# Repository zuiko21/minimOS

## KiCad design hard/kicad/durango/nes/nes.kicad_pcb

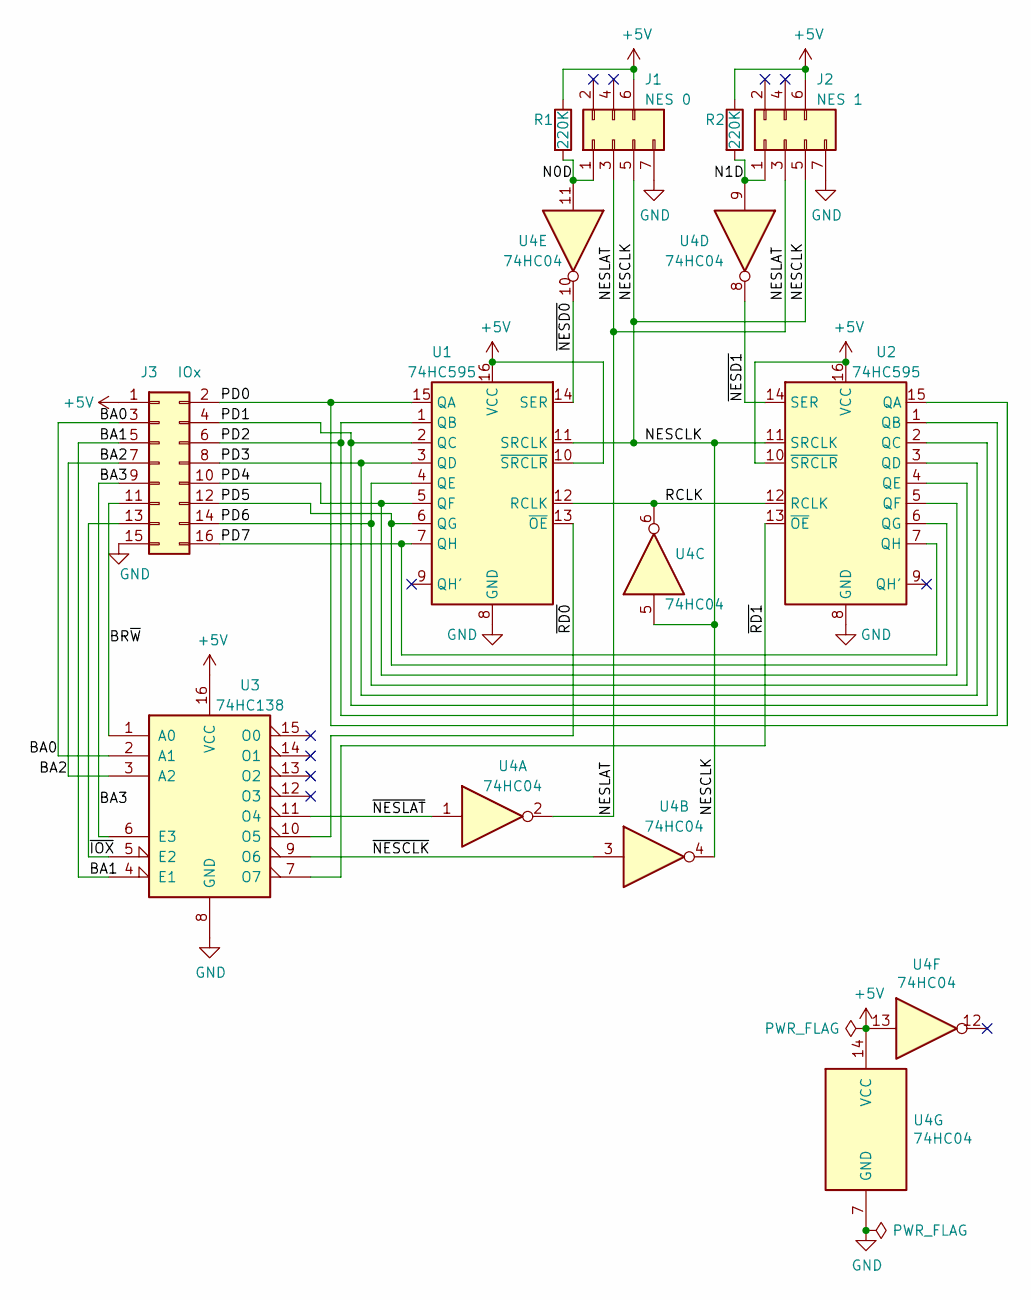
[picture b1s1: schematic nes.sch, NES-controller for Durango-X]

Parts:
J1: NES 0; PinSocket_2x04_P2.54mm_Vertical
J2: NES 1; PinSocket_2x04_P2.54mm_Vertical
J3: IOx; IDC-Header_2x08_P2.54mm_Vertical
R1, R2: 220K; R_Axial_DIN0204_L3.6mm_D1.6mm_P2.54mm_Vertical
U1, U2: 74HC595; DIP-16_W7.62mm_Socket
U3: 74HC138; DIP-16_W7.62mm_Socket
U4: 74HC04; DIP-14_W7.62mm_Socket

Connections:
+5V: J1.6, J2.6, J3.1, R1.1, R2.1, U1.10 (~SRCLR), U1.16 (VCC), U2.10 (~SRCLR), U2.16 (VCC), U3.16 (VCC), U4.13, U4.14 (VCC)
/BA0: J3.3, U3.2 (A1)
/BA1: J3.5, U3.4 (E1)
/BA2: J3.7, U3.3 (A2)
/BA3: J3.9, U3.6 (E3)
/BR~W: J3.11, U3.1 (A0)
/N0D: J1.1, R1.2, U4.11
/N1D: J2.1, R2.2, U4.9
/NESCLK: J1.5, J2.5, U1.11 (SRCLK), U2.11 (SRCLK), U4.4, U4.5
/NESLAT: J1.3, J2.3, U4.2
/PD0: J3.2, U1.15 (QA), U2.15 (QA)
/PD1: J3.4, U1.2 (QC), U2.2 (QC)
/PD2: J3.6, U1.1 (QB), U2.1 (QB)
/PD3: J3.8, U1.3 (QD), U2.3 (QD)
/PD4: J3.10, U1.5 (QF), U2.5 (QF)
/PD5: J3.12, U1.6 (QG), U2.6 (QG)
/PD6: J3.14, U1.4 (QE), U2.4 (QE)
/PD7: J3.16, U1.7 (QH), U2.7 (QH)
/RCLK: U1.12 (RCLK), U2.12 (RCLK), U4.6
/~IOX: J3.13, U3.5 (E2)
/~NESCLK: U3.9 (O6), U4.3
/~NESD0: U1.14 (SER), U4.10
/~NESD1: U2.14 (SER), U4.8
/~NESLAT: U3.11 (O4), U4.1
/~RD0: U1.13 (~OE), U3.10 (O5)
/~RD1: U2.13 (~OE), U3.7 (O7)
GND: J1.7, J2.7, J3.15, U1.8 (GND), U2.8 (GND), U3.8 (GND), U4.7 (GND)

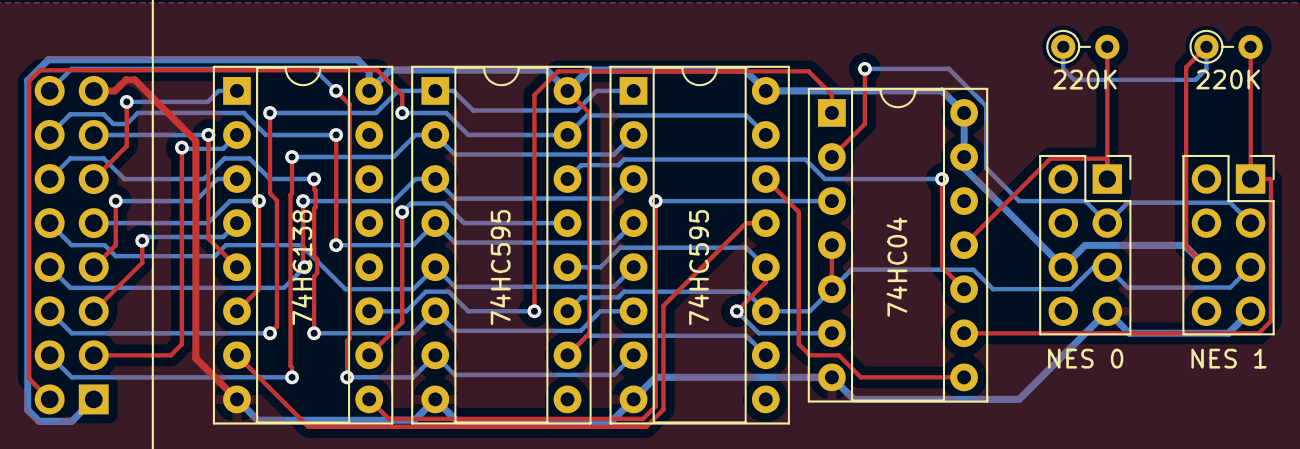
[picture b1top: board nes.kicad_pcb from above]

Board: 2 copper layers, 9 parts (0 on the bottom side), 27 nets.

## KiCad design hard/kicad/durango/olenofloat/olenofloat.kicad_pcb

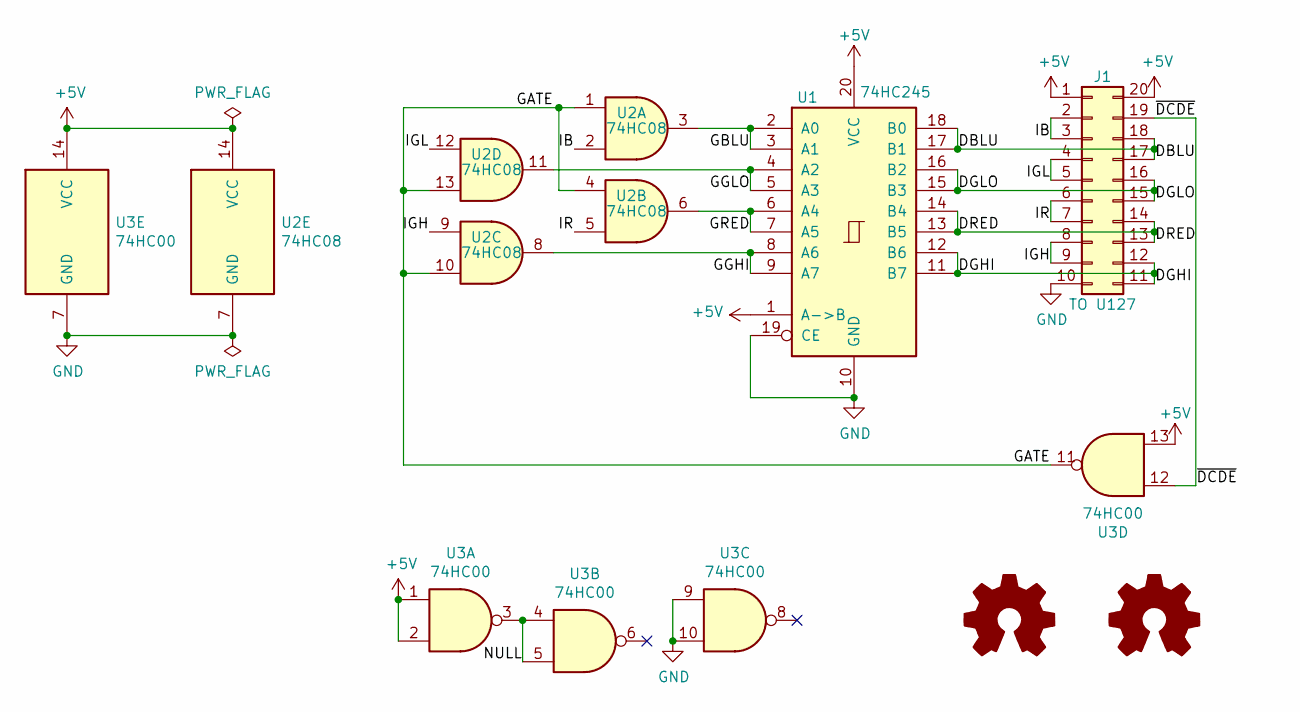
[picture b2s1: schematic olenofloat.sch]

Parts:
J1: TO U127; DIP-20_W7.62mm_Socket_LongPads
LOGO1: Logo_Open_Hardware_Small; j300
LOGO2: Logo_Open_Hardware_Small; OSHW-Symbol_6.7x6mm_SilkScreen
U1: 74HC245; DIP-20_W7.62mm_Socket
U2: 74HC08; DIP-14_W7.62mm_Socket
U3: 74HC00; DIP-14_W7.62mm_Socket

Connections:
+5V: J1.1, J1.20, U1.1 (A->B), U1.20 (VCC), U2.14 (VCC), U3.1, U3.2, U3.13, U3.14 (VCC)
/DBLU: J1.17, J1.18, U1.17 (B1), U1.18 (B0)
/DGHI: J1.11, J1.12, U1.11 (B7), U1.12 (B6)
/DGLO: J1.15, J1.16, U1.15 (B3), U1.16 (B2)
/DRED: J1.13, J1.14, U1.13 (B5), U1.14 (B4)
/GATE: U2.1, U2.4, U2.10, U2.13, U3.11
/GBLU: U1.2 (A0), U1.3 (A1), U2.3
/GGHI: U1.8 (A6), U1.9 (A7), U2.8
/GGLO: U1.4 (A2), U1.5 (A3), U2.11
/GRED: U1.6 (A4), U1.7 (A5), U2.6
/IB: J1.2, J1.3, U2.2
/IGH: J1.8, J1.9, U2.9
/IGL: J1.4, J1.5, U2.12
/IR: J1.6, J1.7, U2.5
/NULL: U3.3, U3.4, U3.5
/~DCDE: J1.19, U3.12
GND: J1.10, U1.10 (GND), U1.19 (CE), U2.7 (GND), U3.7 (GND), U3.9, U3.10

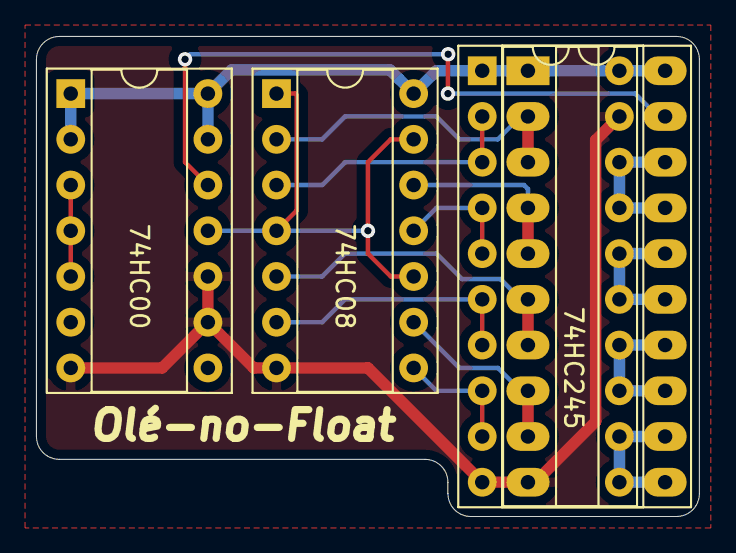
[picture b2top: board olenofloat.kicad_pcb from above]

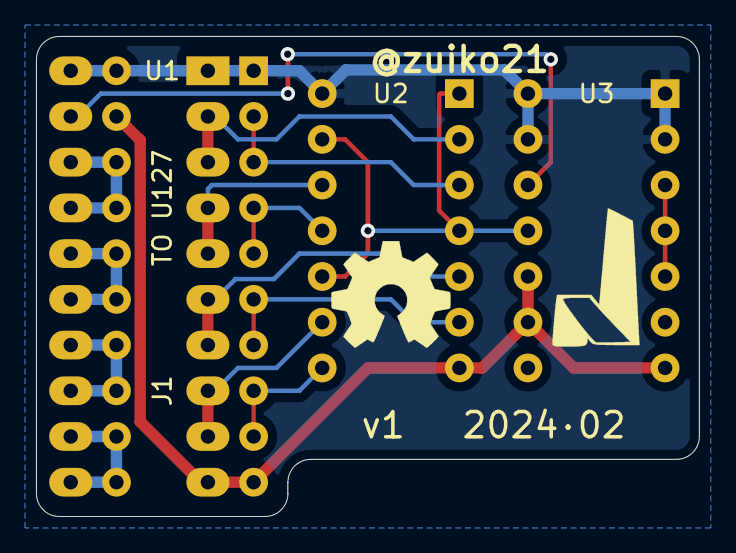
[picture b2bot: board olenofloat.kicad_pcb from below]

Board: 2 copper layers, 36.8 x 26.7 mm, 6 parts (2 on the bottom side), 17 nets.

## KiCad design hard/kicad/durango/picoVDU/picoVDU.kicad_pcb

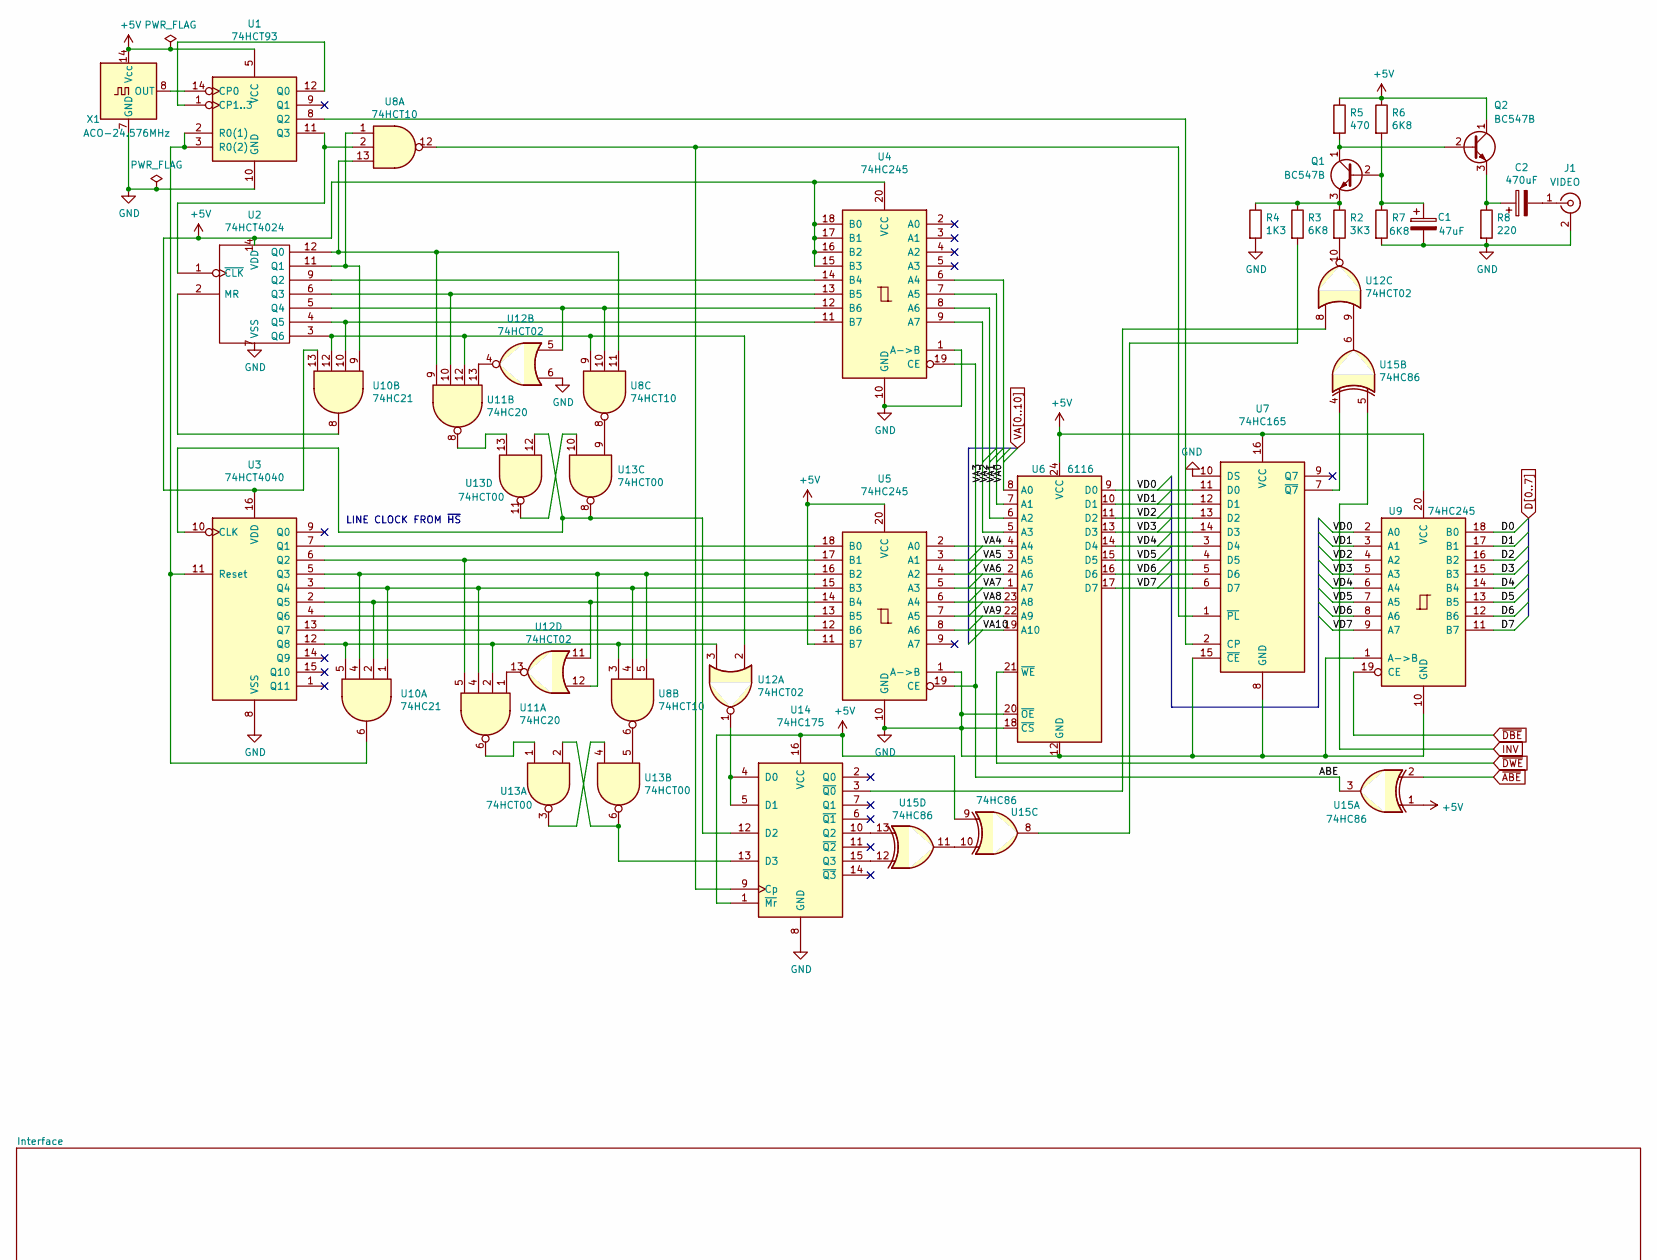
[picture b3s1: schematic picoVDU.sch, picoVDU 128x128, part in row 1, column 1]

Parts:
C1: 47uF; CP_Radial_D8.0mm_P5.00mm
C2: 470uF; CP_Radial_D12.5mm_P5.00mm
J1: VIDEO; SMA_Amphenol_132289_EdgeMount
Q1, Q2: BC547B; TO-92_Inline
R2: 3K3; R_Axial_DIN0309_L9.0mm_D3.2mm_P2.54mm_Vertical
R3, R6, R7: 6K8; R_Axial_DIN0309_L9.0mm_D3.2mm_P2.54mm_Vertical
R4: 1K3; R_Axial_DIN0309_L9.0mm_D3.2mm_P2.54mm_Vertical
R5: 470; R_Axial_DIN0309_L9.0mm_D3.2mm_P2.54mm_Vertical
R8: 220; R_Axial_DIN0309_L9.0mm_D3.2mm_P2.54mm_Vertical
U1: 74HCT93; DIP-14_W7.62mm_Socket
U2: 74HCT4024; DIP-14_W7.62mm_Socket
U3: 74HCT4040; DIP-16_W7.62mm_Socket
U4, U5, U9: 74HC245; DIP-20_W7.62mm_Socket
U6: 6116; DIP-24_W15.24mm_Socket
U7: 74HC165; DIP-16_W7.62mm_Socket
U8: 74HCT10; DIP-14_W7.62mm_Socket
U10: 74HC21; DIP-14_W7.62mm_Socket
U11: 74HC20; DIP-14_W7.62mm_Socket
U12: 74HCT02; DIP-14_W7.62mm_Socket
U13: 74HCT00; DIP-14_W7.62mm_Socket
U14: 74HC175; DIP-16_W7.62mm_Socket
U15: 74HC86; DIP-14_W7.62mm_Socket
X1: ACO-24.576MHz; Oscillator_DIP-14

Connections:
+5V: Q2.1 (C), R5.1, R6.1, U1.5 (VCC), U2.14 (VDD), U3.16 (VDD), U4.15 (B3), U4.16 (B2), U4.17 (B1), U4.18 (B0), U4.20 (VCC), U5.11 (B7), U5.20 (VCC), U6.24 (VCC), U7.16 (VCC), U9.20 (VCC), U10.13, U14.1 (~Mr), U14.16 (VCC), U15.1, U15.9, X1.14 (Vcc); also elsewhere on the board
/ABE: U4.19 (CE), U5.19 (CE), U15.3
/VD0: U6.9 (D0), U7.11 (D0), U9.2 (A0)
/VD1: U6.10 (D1), U7.12 (D1), U9.3 (A1)
/VD2: U6.11 (D2), U7.13 (D2), U9.4 (A2)
/VD3: U6.13 (D3), U7.14 (D3), U9.5 (A3)
/VD4: U6.14 (D4), U7.3 (D4), U9.6 (A4)
/VD5: U6.15 (D5), U7.4 (D5), U9.7 (A5)
/VD6: U6.16 (D6), U7.5 (D6), U9.8 (A6)
/VD7: U6.17 (D7), U7.6 (D7), U9.9 (A7)
D0: U9.18 (B0); also elsewhere on the board
D1: U9.17 (B1); also elsewhere on the board
D2: U9.16 (B2); also elsewhere on the board
D3: U9.15 (B3); also elsewhere on the board
D4: U9.14 (B4); also elsewhere on the board
D5: U9.13 (B5); also elsewhere on the board
D6: U9.12 (B6); also elsewhere on the board
D7: U9.11 (B7); also elsewhere on the board
GND: C1.2, J1.2 (Ext), R4.2, R7.2, R8.2, U1.10 (GND), U2.7 (VSS), U3.8 (VSS), U4.1 (A->B), U4.10 (GND), U5.1 (A->B), U5.10 (GND), U6.12 (GND), U6.18 (~CS), U6.20 (~OE), U7.8 (GND), U7.10 (DS), U7.15 (~CE), U9.1 (A->B), U9.10 (GND), U12.6, U14.8 (GND), X1.7 (GND); also elsewhere on the board
INV: U15.5; also elsewhere on the board
unnamed: C1.1, Q1.2 (B), R6.2, R7.1
unnamed: C2.1, Q2.3 (E), R8.1
unnamed: C2.2, J1.1 (In)
unnamed: Q1.1 (C), Q2.2 (B), R5.2
unnamed: Q1.3 (E), R2.1, R3.1, R4.1
unnamed: R2.2, U12.10
unnamed: R3.2, U15.8
unnamed: U1.1 (CP1..3), U1.12 (Q0)
unnamed: U1.2 (R0(1)), U1.3 (R0(2)), U3.11 (Reset), U10.6
unnamed: U1.8 (Q2), U7.2 (CP)
unnamed: U1.11 (Q3), U2.1 (~CLK), U8.2
unnamed: U1.14 (CP0), X1.8 (OUT)
unnamed: U2.9 (Q2), U4.14 (B4)
unnamed: U3.4 (Q6), U5.13 (B5)
unnamed: U3.7 (Q1), U5.18 (B0)
unnamed: U3.13 (Q7), U5.12 (B6)
unnamed: U3.3 (Q4), U5.15 (B3), U8.4, U10.1, U11.4
unnamed: U3.2 (Q5), U5.14 (B4), U10.2, U12.11
unnamed: U3.5 (Q3), U5.16 (B2), U8.5, U10.4, U12.12
unnamed: U3.12 (Q8), U8.3, U10.5, U11.2, U12.3
unnamed: U2.2 (MR), U10.8
unnamed: U2.11 (Q1), U8.1, U10.9
unnamed: U2.4 (Q5), U4.11 (B7), U10.10
unnamed: U2.3 (Q6), U8.9, U10.12, U11.12, U12.2
unnamed: U11.1, U12.13
unnamed: U3.6 (Q2), U5.17 (B1), U11.5
unnamed: U11.6, U13.1
unnamed: U11.8, U13.13
unnamed: U2.12 (Q0), U8.11, U8.13, U11.9
unnamed: U2.6 (Q3), U4.13 (B5), U11.10
unnamed: U11.13, U12.4
unnamed: U12.1, U14.4 (D0), U14.5 (D1)
unnamed: U2.5 (Q4), U4.12 (B6), U8.10, U12.5
unnamed: U12.8, U14.3 (~Q0)
unnamed: U12.9, U15.6
unnamed: U13.2, U13.6, U14.13 (D3)
unnamed: U13.3, U13.4
unnamed: U8.6, U13.5
unnamed: U8.8, U13.9
unnamed: U13.10, U13.11
unnamed: U3.10 (CLK), U13.8, U13.12, U14.12 (D2)
unnamed: U7.1 (~PL), U8.12, U14.9 (Cp)
unnamed: U14.10 (Q2), U15.13
unnamed: U14.15 (Q3), U15.12
unnamed: U7.7 (~Q7), U15.4
unnamed: U15.10, U15.11
VA0: U4.6 (A4), U6.8 (A0); also elsewhere on the board
VA1: U4.7 (A5), U6.7 (A1); also elsewhere on the board
VA2: U4.8 (A6), U6.6 (A2); also elsewhere on the board
VA3: U4.9 (A7), U6.5 (A3); also elsewhere on the board
VA4: U5.2 (A0), U6.4 (A4); also elsewhere on the board
VA5: U5.3 (A1), U6.3 (A5); also elsewhere on the board
VA6: U5.4 (A2), U6.2 (A6); also elsewhere on the board
VA7: U5.5 (A3), U6.1 (A7); also elsewhere on the board
VA8: U5.6 (A4), U6.23 (A8); also elsewhere on the board
VA9: U5.7 (A5), U6.22 (A9); also elsewhere on the board
VA10: U5.8 (A6), U6.19 (A10); also elsewhere on the board
~ABE: U15.2; also elsewhere on the board
~DBE: U6.21 (~WE), U9.19 (CE); also elsewhere on the board

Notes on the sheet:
LINE CLOCK FROM ~HS

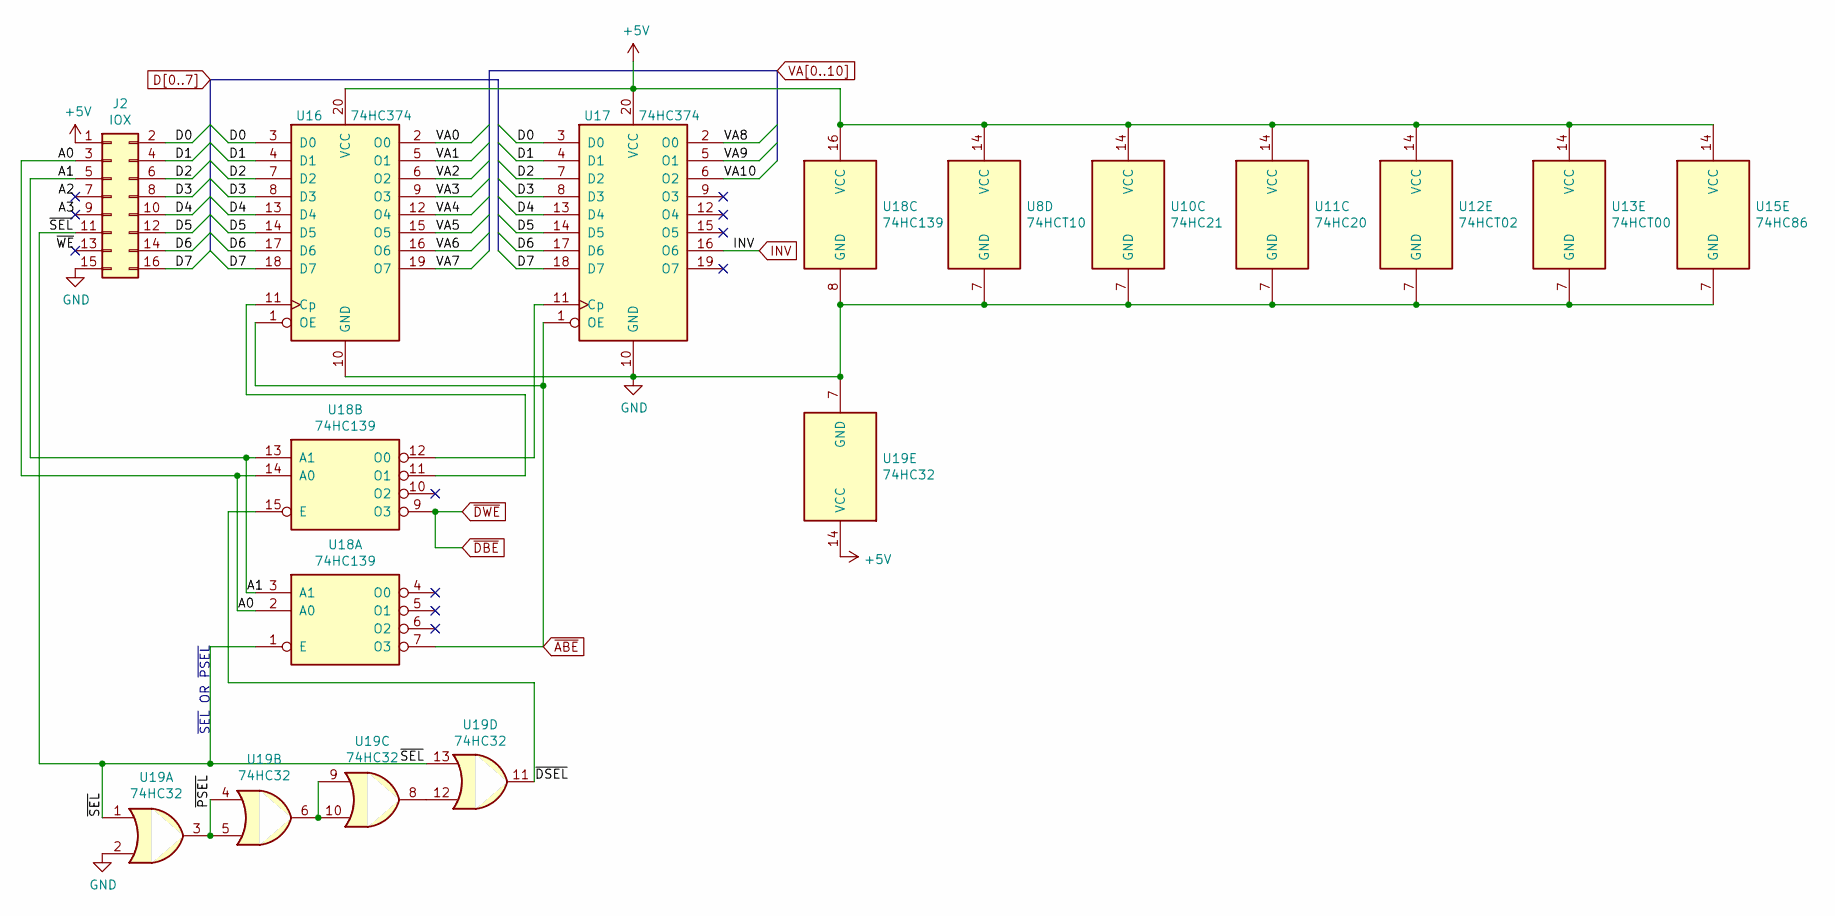
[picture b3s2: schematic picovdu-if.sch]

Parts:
J2: IOX; PinHeader_2x08_P2.54mm_Vertical
U8: 74HCT10; DIP-14_W7.62mm_Socket
U10: 74HC21; DIP-14_W7.62mm_Socket
U11: 74HC20; DIP-14_W7.62mm_Socket
U12: 74HCT02; DIP-14_W7.62mm_Socket
U13: 74HCT00; DIP-14_W7.62mm_Socket
U15: 74HC86; DIP-14_W7.62mm_Socket
U16, U17: 74HC374; DIP-20_W7.62mm_Socket
U18: 74HC139; DIP-16_W7.62mm_Socket
U19: 74HC32; DIP-14_W7.62mm_Socket

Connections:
+5V: J2.1, U8.14 (VCC), U10.14 (VCC), U11.14 (VCC), U12.14 (VCC), U13.14 (VCC), U15.14 (VCC), U16.20 (VCC), U17.20 (VCC), U18.16 (VCC), U19.14 (VCC); also elsewhere on the board
/Interface/A0: J2.3, U18.2 (A0), U18.14 (A0)
/Interface/A1: J2.5, U18.3 (A1), U18.13 (A1)
/Interface/A2: J2.7
/Interface/A3: J2.9
/Interface/~DSEL: U18.15 (E), U19.11
/Interface/~PSEL: U19.3, U19.4, U19.5
/Interface/~SEL: J2.11, U18.1 (E), U19.1, U19.13
/Interface/~WE: J2.13
D0: J2.2, U16.3 (D0), U17.3 (D0); also elsewhere on the board
D1: J2.4, U16.4 (D1), U17.4 (D1); also elsewhere on the board
D2: J2.6, U16.7 (D2), U17.7 (D2); also elsewhere on the board
D3: J2.8, U16.8 (D3), U17.8 (D3); also elsewhere on the board
D4: J2.10, U16.13 (D4), U17.13 (D4); also elsewhere on the board
D5: J2.12, U16.14 (D5), U17.14 (D5); also elsewhere on the board
D6: J2.14, U16.17 (D6), U17.17 (D6); also elsewhere on the board
D7: J2.16, U16.18 (D7), U17.18 (D7); also elsewhere on the board
GND: J2.15, U8.7 (GND), U10.7 (GND), U11.7 (GND), U12.7 (GND), U13.7 (GND), U15.7 (GND), U16.10 (GND), U17.10 (GND), U18.8 (GND), U19.2, U19.7 (GND); also elsewhere on the board
INV: U17.16 (O6); also elsewhere on the board
unnamed: U16.11 (Cp), U18.11 (O1)
unnamed: U17.11 (Cp), U18.12 (O0)
unnamed: U19.6, U19.9, U19.10
unnamed: U19.8, U19.12
VA0: U16.2 (O0); also elsewhere on the board
VA1: U16.5 (O1); also elsewhere on the board
VA2: U16.6 (O2); also elsewhere on the board
VA3: U16.9 (O3); also elsewhere on the board
VA4: U16.12 (O4); also elsewhere on the board
VA5: U16.15 (O5); also elsewhere on the board
VA6: U16.16 (O6); also elsewhere on the board
VA7: U16.19 (O7); also elsewhere on the board
VA8: U17.2 (O0); also elsewhere on the board
VA9: U17.5 (O1); also elsewhere on the board
VA10: U17.6 (O2); also elsewhere on the board
~ABE: U16.1 (OE), U17.1 (OE), U18.7 (O3); also elsewhere on the board
~DBE: U18.9 (O3); also elsewhere on the board

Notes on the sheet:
~SEL~ OR ~PSEL

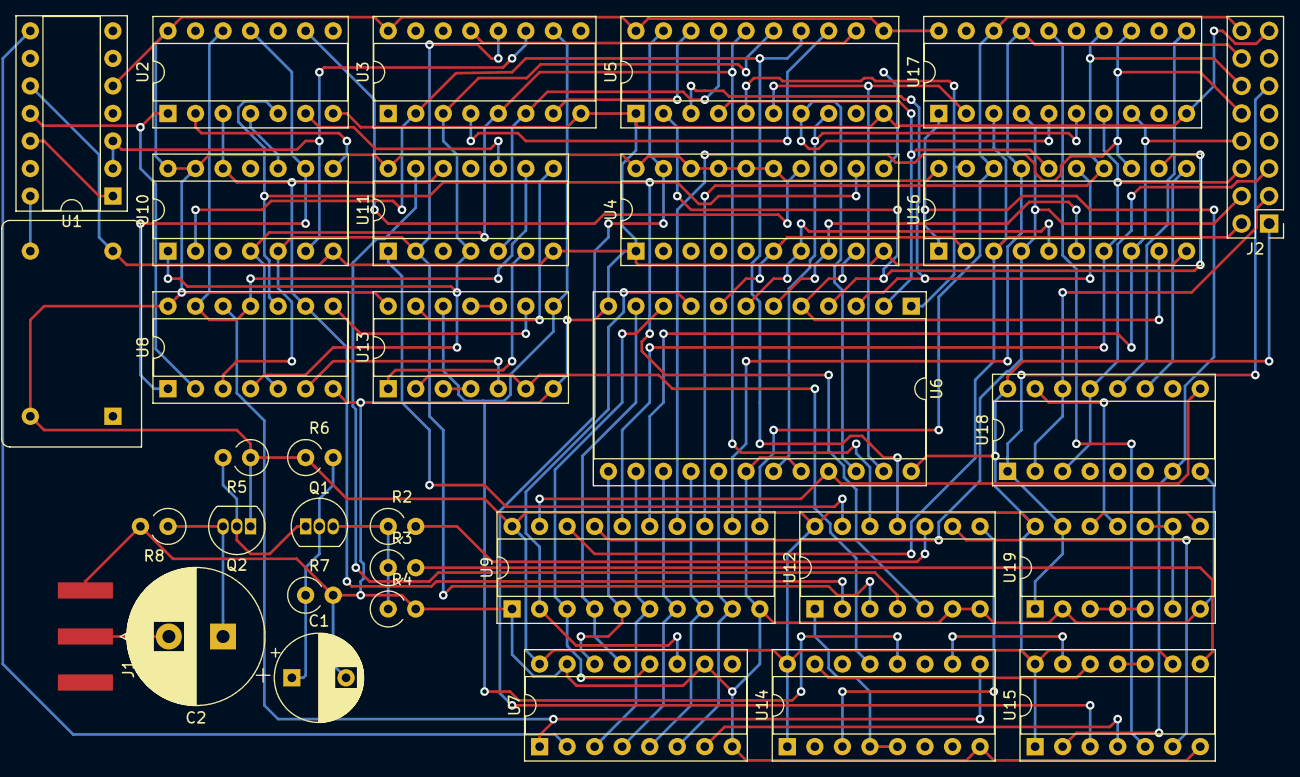
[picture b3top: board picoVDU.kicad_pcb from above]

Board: 2 copper layers, 33 parts (0 on the bottom side), 88 nets.

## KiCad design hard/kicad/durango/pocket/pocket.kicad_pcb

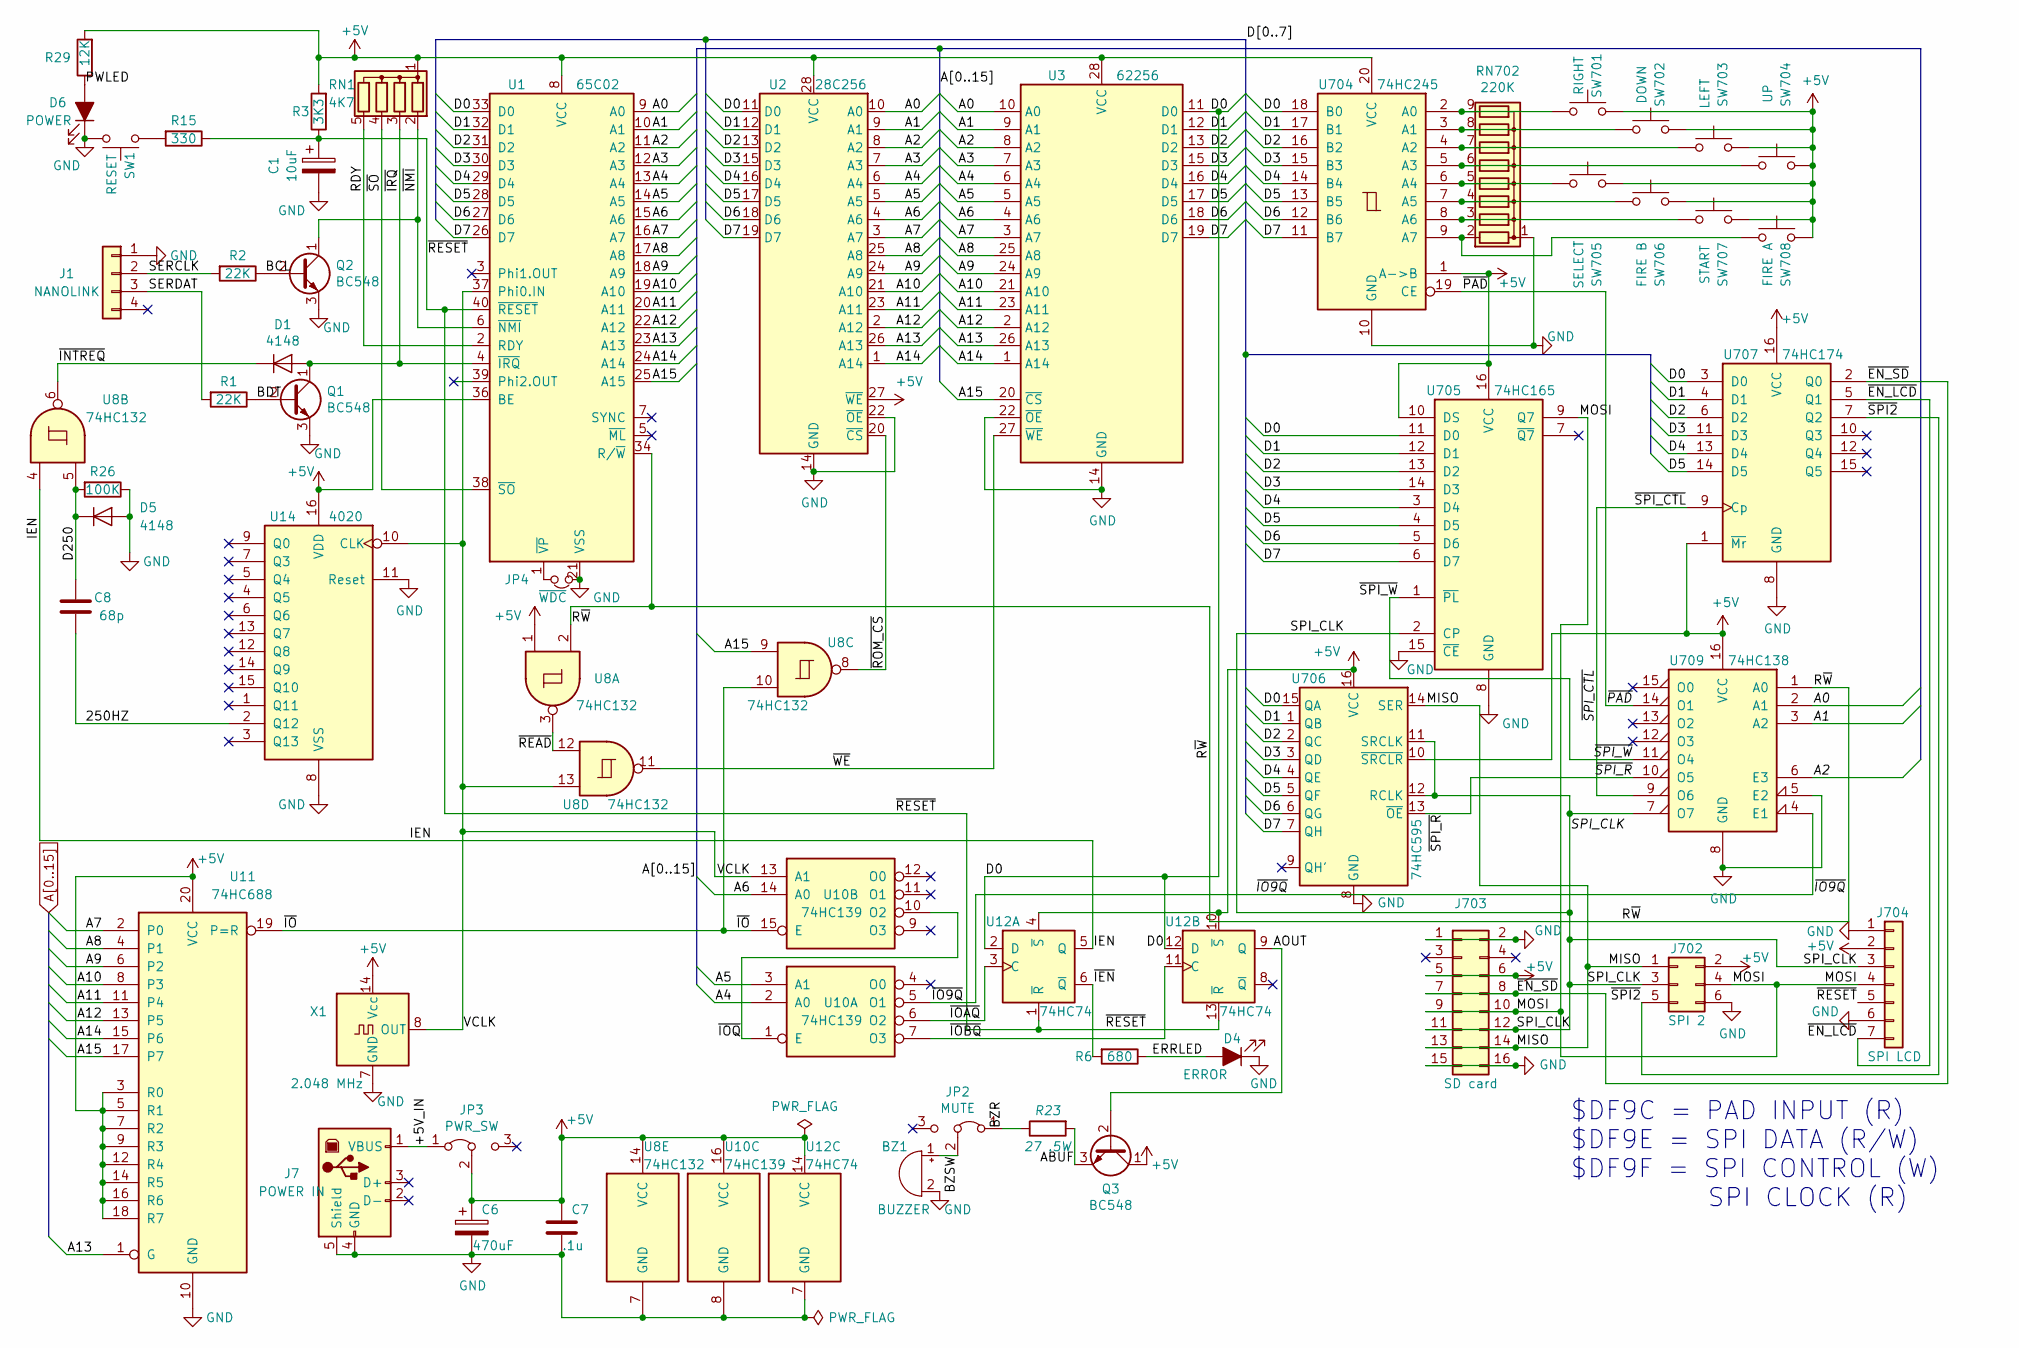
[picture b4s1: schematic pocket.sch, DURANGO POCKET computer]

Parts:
BZ1: BUZZER; Buzzer_12x9.5RM7.6
C1: 10uF; CP_Radial_D4.0mm_P1.50mm
C6: 470uF; CP_Radial_D6.3mm_P2.50mm
C7: .1u; C_Rect_L7.2mm_W2.5mm_P5.00mm_FKS2_FKP2_MKS2_MKP2
C8: 68p; C_Disc_D3.8mm_W2.6mm_P2.50mm
D1, D5: 4148; D_DO-35_SOD27_P2.54mm_Vertical_KathodeUp
D4: ERROR; LED_D3.0mm_Clear
D6: POWER; LED_D3.0mm_Clear
J1: NANOLINK; PinHeader_1x04_P2.54mm_Vertical
J7: POWER IN; USB_B_OST_USB-B1HSxx_Horizontal
J702: SPI 2; PinSocket_2x03_P2.54mm_Horizontal
J703: SD card; PinHeader_2x08_P2.54mm_Vertical
J704: SPI LCD; PinHeader_1x07_P2.54mm_Vertical
JP2: MUTE; Switch_Slide_11.6x4mm_EG1218
JP3: PWR_SW; Switch_Slide_11.6x4mm_EG1218
JP4: ~WDC; SolderJumper-2_P1.3mm_Open_RoundedPad1.0x1.5mm
Q1, Q2, Q3: BC548; TO-92_Inline
R1, R2: 22K; R_Axial_DIN0207_L6.3mm_D2.5mm_P2.54mm_Vertical
R3: 3K3; R_Axial_DIN0207_L6.3mm_D2.5mm_P2.54mm_Vertical
R6: 680; R_Axial_DIN0207_L6.3mm_D2.5mm_P2.54mm_Vertical
R15: 330; R_Axial_DIN0207_L6.3mm_D2.5mm_P2.54mm_Vertical
R23: 27 .5W; R_Axial_DIN0309_L9.0mm_D3.2mm_P2.54mm_Vertical
R26: 100K; R_Axial_DIN0207_L6.3mm_D2.5mm_P2.54mm_Vertical
R29: 12K; R_Axial_DIN0207_L6.3mm_D2.5mm_P2.54mm_Vertical
RN1: 4K7; R_Array_SIP5
RN702: 220K; R_Array_SIP9
SW1: RESET; SW_PUSH_6mm
SW701: RIGHT; SW_PUSH_6mm
SW702: DOWN; SW_PUSH_6mm
SW703: LEFT; SW_PUSH_6mm
SW704: UP; SW_PUSH_6mm
SW705: SELECT; SW_PUSH_6mm
SW706: FIRE B; SW_PUSH_6mm
SW707: START; SW_PUSH_6mm
SW708: FIRE A; SW_PUSH_6mm
U1: 65C02; DIP-40_W15.24mm_Socket
U2: 28C256; DIP-28_W15.24mm_Socket
U3: 62256; DIP-28_W15.24mm_Socket
U8: 74HC132; DIP-14_W7.62mm_Socket
U10: 74HC139; DIP-16_W7.62mm_Socket
U11: 74HC688; DIP-20_W7.62mm_Socket
U12: 74HC74; DIP-14_W7.62mm_Socket
U14: 4020; DIP-16_W7.62mm_Socket
U704: 74HC245; DIP-20_W7.62mm_Socket
U705: 74HC165; DIP-16_W7.62mm_Socket
U706: 74HC595; DIP-16_W7.62mm_Socket
U707: 74HC174; DIP-16_W7.62mm_Socket
U709: 74HC138; DIP-16_W7.62mm_Socket
X1: 2.048 MHz; Oscillator_DIP-14

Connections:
+5V: C6.1, C7.1, J702.2, J703.5, J703.6, J704.2, JP3.2 (C), Q3.1 (C), R3.2, R29.2, RN1.1 (common), SW701.1, SW702.1, SW703.1, SW704.1, SW705.1, SW706.1, SW707.1, SW708.1, U1.8 (VCC), U1.36 (BE), U2.27 (~WE), U2.28 (VCC), U3.28 (VCC), U8.1, U8.14 (VCC), U10.16 (VCC), U11.3 (R0), U11.5 (R1), U11.7 (R2), U11.9 (R3), U11.12 (R4), U11.14 (R5), U11.16 (R6), U11.18 (R7), U11.20 (VCC), U12.4 (~S), U12.10 (~S), U12.14 (VCC), U14.16 (VDD), U704.1 (A->B), U704.20 (VCC), U705.10 (DS), U705.16 (VCC), U706.10 (~SRCLR), U706.16 (VCC), U707.1 (~Mr), U707.16 (VCC), U709.16 (VCC), X1.14 (Vcc)
/250HZ: C8.1, U14.2 (Q12)
/+5V_IN: J7.1 (VBUS), JP3.1 (A)
/ABUF: Q3.3 (E), R23.2
/AOUT: Q3.2 (B), U12.9 (Q)
/BCL: Q2.2 (B), R2.1
/BDT: Q1.2 (B), R1.1
/BZR: JP2.1 (A), R23.1
/BZSW: BZ1.1 (-), JP2.2 (C)
/D0: U1.33 (D0), U2.11 (D0), U3.11 (D0), U12.2 (D), U12.12 (D), U704.18 (B0), U705.11 (D0), U706.15 (QA), U707.3 (D0)
/D1: U1.32 (D1), U2.12 (D1), U3.12 (D1), U704.17 (B1), U705.12 (D1), U706.1 (QB), U707.4 (D1)
/D2: U1.31 (D2), U2.13 (D2), U3.13 (D2), U704.16 (B2), U705.13 (D2), U706.2 (QC), U707.6 (D2)
/D3: U1.30 (D3), U2.15 (D3), U3.15 (D3), U704.15 (B3), U705.14 (D3), U706.3 (QD), U707.11 (D3)
/D4: U1.29 (D4), U2.16 (D4), U3.16 (D4), U704.14 (B4), U705.3 (D4), U706.4 (QE), U707.13 (D4)
/D5: U1.28 (D5), U2.17 (D5), U3.17 (D5), U704.13 (B5), U705.4 (D5), U706.5 (QF), U707.14 (D5)
/D6: U1.27 (D6), U2.18 (D6), U3.18 (D6), U704.12 (B6), U705.5 (D6), U706.6 (QG)
/D7: U1.26 (D7), U2.19 (D7), U3.19 (D7), U704.11 (B7), U705.6 (D7), U706.7 (QH)
/D250: C8.2, D5.1 (K), R26.2, U8.5
/ERRLED: D4.2 (A), R6.1
/IEN: U8.4, U12.5 (Q)
/MISO: J702.1, J703.13, J703.14, U706.14 (SER)
/MOSI: J702.4, J703.9, J703.10, J704.4, U705.9 (Q7)
/PWLED: D6.2 (A), R29.1
/RDY: RN1.5 (R4), U1.2 (RDY)
/R~W: U1.34 (R/~W), U8.2, U709.1 (A0)
/SERCLK: J1.2, R2.2
/SERDAT: J1.3, R1.2
/SPI_CLK: J702.3, J703.11, J703.12, J704.3, U705.2 (CP), U706.11 (SRCLK), U706.12 (RCLK), U709.7 (O7)
/VCLK: U1.37 (Phi0.IN), U8.13, U10.13 (A1), U14.10 (CLK), X1.8 (OUT)
/~EN_LCD: J704.7, U707.5 (Q1)
/~EN_SD: J703.7, J703.8, U707.2 (Q0)
/~IEN: R6.2, U12.6 (~Q)
/~INTREQ: D1.1 (K), U8.6
/~IO: U8.10, U10.15 (E), U11.19 (P=R)
/~IO9Q: U10.5 (O1), U709.4 (E1)
/~IOAQ: U10.6 (O2), U12.3 (C)
/~IOBQ: U10.7 (O3), U12.11 (C)
/~IOQ: U10.1 (E), U10.10 (O2)
/~IRQ: D1.2 (A), Q1.1 (C), RN1.3 (R2), U1.4 (~IRQ)
/~NMI: Q2.1 (C), RN1.2 (R1), U1.6 (~NMI)
/~PAD: U704.19 (CE), U709.14 (O1)
/~READ: U8.3, U8.12
/~RESET: C1.1, J704.5, R3.1, R15.1, U1.40 (~RESET), U12.1 (~R), U12.13 (~R)
/~ROM_CS: U2.20 (~CS), U8.8
/~SO: RN1.4 (R3), U1.38 (~SO)
/~SPI2: J702.5, U707.7 (Q2)
/~SPI_CTL: U707.9 (Cp), U709.9 (O6)
/~SPI_R: U706.13 (~OE), U709.10 (O5)
/~SPI_W: U705.1 (~PL), U709.11 (O4)
/~WE: U3.27 (~WE~), U8.11
A0: U1.9 (A0), U2.10 (A0), U3.10 (A0), U709.2 (A1)
A1: U1.10 (A1), U2.9 (A1), U3.9 (A1), U709.3 (A2)
A2: U1.11 (A2), U2.8 (A2), U3.8 (A2), U709.6 (E3)
A3: U1.12 (A3), U2.7 (A3), U3.7 (A3)
A4: U1.13 (A4), U2.6 (A4), U3.6 (A4), U10.2 (A0)
A5: U1.14 (A5), U2.5 (A5), U3.5 (A5), U10.3 (A1)
A6: U1.15 (A6), U2.4 (A6), U3.4 (A6), U10.14 (A0)
A7: U1.16 (A7), U2.3 (A7), U3.3 (A7), U11.2 (P0)
A8: U1.17 (A8), U2.25 (A8), U3.25 (A8), U11.4 (P1)
A9: U1.18 (A9), U2.24 (A9), U3.24 (A9), U11.6 (P2)
A10: U1.19 (A10), U2.21 (A10), U3.21 (A10), U11.8 (P3)
A11: U1.20 (A11), U2.23 (A11), U3.23 (A11), U11.11 (P4)
A12: U1.22 (A12), U2.2 (A12), U3.2 (A12), U11.13 (P5)
A13: U1.23 (A13), U2.26 (A13), U3.26 (A13), U11.1 (G)
A14: U1.24 (A14), U2.1 (A14), U3.1 (A14), U11.15 (P6)
A15: U1.25 (A15), U3.20 (~CS), U8.9, U11.17 (P7)
GND: BZ1.2 (+), C1.2, C6.2, C7.2, D4.1 (K), D5.2 (A), D6.1 (K), J1.1, J7.4 (GND), J7.5 (Shield), J702.6, J703.1, J703.2, J703.15, J703.16, J704.1, J704.6, JP4.2, Q1.3 (E), Q2.3 (E), R26.1, RN702.1 (common), SW1.2, U1.21 (VSS), U2.14 (GND), U2.22 (~OE), U3.14 (GND), U3.22 (~OE~), U8.7 (GND), U10.8 (GND), U11.10 (GND), U12.7 (GND), U14.8 (VSS), U14.11 (Reset), U704.10 (GND), U705.8 (GND), U705.15 (~CE), U706.8 (GND), U707.8 (GND), U709.5 (E2), U709.8 (GND), X1.7 (GND)
unnamed: JP4.1, U1.1 (~VP)
unnamed: R15.2, SW1.1
unnamed: RN702.2 (R1), SW708.2, U704.9 (A7)
unnamed: RN702.3 (R2), SW707.2, U704.8 (A6)
unnamed: RN702.4 (R3), SW706.2, U704.7 (A5)
unnamed: RN702.5 (R4), SW705.2, U704.6 (A4)
unnamed: RN702.6 (R5), SW704.2, U704.5 (A3)
unnamed: RN702.7 (R6), SW703.2, U704.4 (A2)
unnamed: RN702.8 (R7), SW702.2, U704.3 (A1)
unnamed: RN702.9 (R8), SW701.2, U704.2 (A0)

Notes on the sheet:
$DF9C = PAD INPUT (R) $DF9E = SPI DATA (R/W) $DF9F = SPI CONTROL (W) SPI CLOCK (R)

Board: 2 copper layers, 53 parts (0 on the bottom side), 77 nets, no tracks yet.

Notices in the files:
hard/kicad/durango/pocket/pocket.sch:
(c) 2023 Carlos J. Santisteban
hard/kicad/durango/viaport/viaport.sch:
(c) 2012-2024 Carlos J. Santisteban
